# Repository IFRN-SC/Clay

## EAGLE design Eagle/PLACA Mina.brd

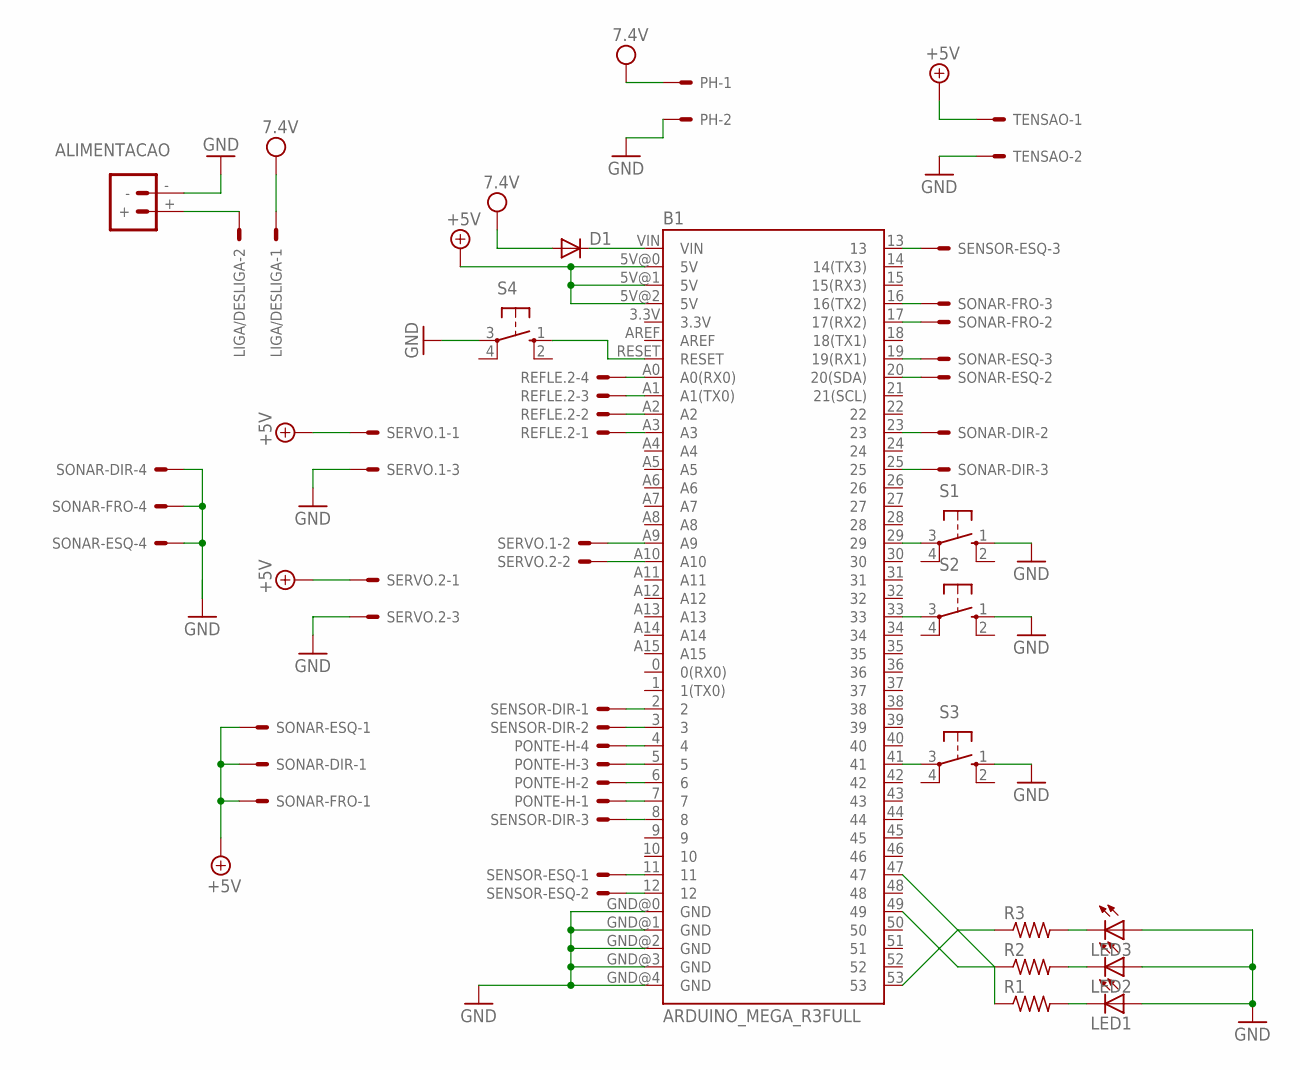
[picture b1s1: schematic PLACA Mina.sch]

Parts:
ALIMENTACAO: BATTERY_CONNXT60; XT60
B1: ARDUINO_MEGA_R3FULL; ARDUINO_MEGA
D1: 1N4004; DO41-10
LED1, LED2, LED3: LED5MM
LIGA/DESLIGA: CONN_0227-2021; 6410-02
PH: CONN_0227-2021; 6410-02
PONTE-H: CONN_0427-2041; 6410-04
R1, R2, R3: R-US_0204/7; 0204/7
REFLE.2: CONN_0427-2041; 6410-04
S1, S2, S3, S4: 10-XX; B3F-10XX
SENSOR-DIR: CONN_0327-2031; 6410-03
SENSOR-ESQ: CONN_0327-2031; 6410-03
SERVO.1, SERVO.2: CONN_0327-2031; 6410-03
SONAR-DIR: CONN_0427-2041; 6410-04
SONAR-ESQ: CONN_0427-2041; 6410-04
SONAR-FRO: CONN_0427-2041; 6410-04
TENSAO: CONN_0227-2021; 6410-02

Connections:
+5V: B1.5V@0 (5V), B1.5V@1 (5V), B1.5V@2 (5V), SERVO.1.1, SERVO.2.1, SONAR-DIR.1, SONAR-ESQ.1, SONAR-FRO.1, TENSAO.1
GND: ALIMENTACAO.-, B1.GND@0 (GND), B1.GND@1 (GND), B1.GND@2 (GND), B1.GND@3 (GND), B1.GND@4 (GND), LED1.A, LED2.A, LED3.A, PH.2, S1.1 (S), S2.1 (S), S3.1 (S), S4.3, SERVO.1.3, SERVO.2.3, SONAR-DIR.4, SONAR-ESQ.4, SONAR-FRO.4, TENSAO.2
unnamed: B1.A3, REFLE.2.1
unnamed: B1.A2, REFLE.2.2
unnamed: B1.A1 (A1(TX0)), REFLE.2.3
unnamed: B1.A0 (A0(RX0)), REFLE.2.4
unnamed: B1.16 (16(TX2)), SONAR-FRO.3
unnamed: B1.17 (17(RX2)), SONAR-FRO.2
unnamed: B1.7, PONTE-H.1
unnamed: B1.6, PONTE-H.2
unnamed: B1.5, PONTE-H.3
unnamed: B1.4, PONTE-H.4
unnamed: B1.20 (20(SDA)), SONAR-ESQ.2
unnamed: B1.19 (19(RX1)), SONAR-ESQ.3
unnamed: B1.23, SONAR-DIR.2
unnamed: B1.25, SONAR-DIR.3
unnamed: B1.11, SENSOR-ESQ.1
unnamed: B1.12, SENSOR-ESQ.2
unnamed: B1.13, SENSOR-ESQ.3
unnamed: B1.2, SENSOR-DIR.1
unnamed: B1.3, SENSOR-DIR.2
unnamed: B1.8, SENSOR-DIR.3
unnamed: B1.A10, SERVO.2.2
unnamed: B1.A9, SERVO.1.2
unnamed: B1.29, S1.3
unnamed: B1.33, S2.3
unnamed: B1.41, S3.3
unnamed: B1.53, R3.1
unnamed: B1.49, R2.1
unnamed: B1.47, R1.1
unnamed: LED1.K (C), R1.2
unnamed: LED2.K (C), R2.2
unnamed: LED3.K (C), R3.2
unnamed: B1.VIN, D1.C
unnamed: ALIMENTACAO.+, LIGA/DESLIGA.2
unnamed: B1.RESET, S4.1 (S)
VDD: D1.A, LIGA/DESLIGA.1, PH.1

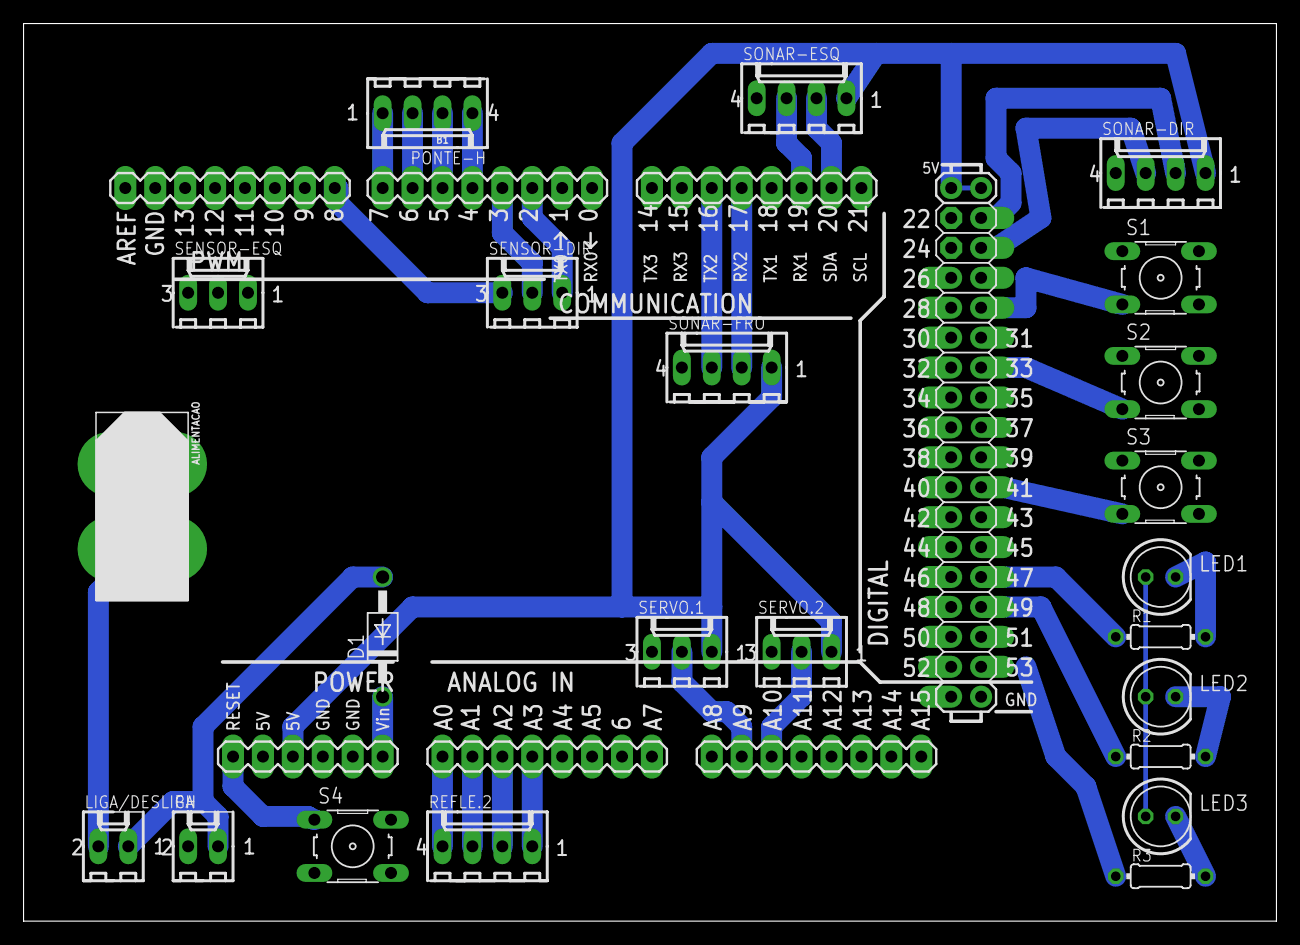
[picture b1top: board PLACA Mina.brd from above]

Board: 2 copper layers, 106.3 x 76.2 mm, 24 parts (0 on the bottom side), 37 nets.

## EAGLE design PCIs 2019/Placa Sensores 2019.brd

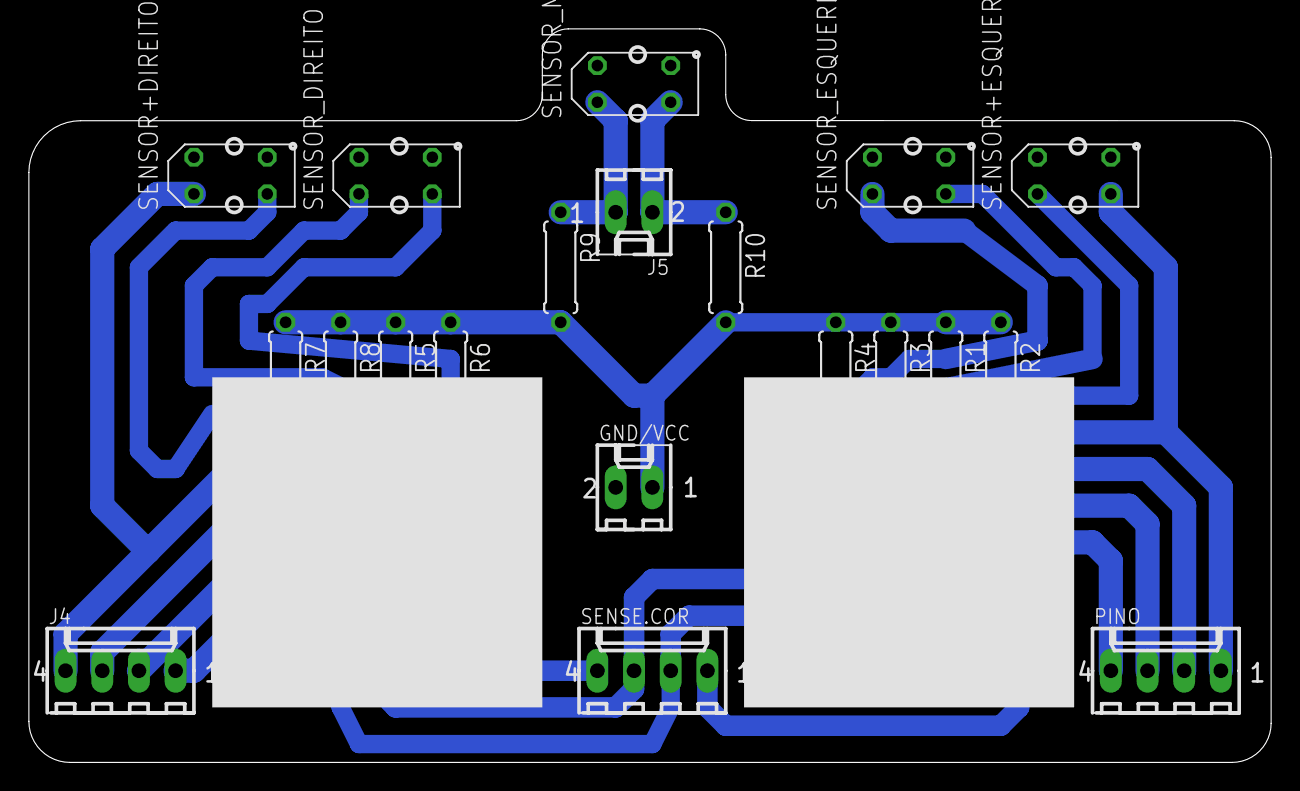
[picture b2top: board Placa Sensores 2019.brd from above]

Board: 2 copper layers, 86.0 x 50.8 mm, 22 parts (0 on the bottom side), 16 nets.

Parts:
GND/VCC: TENSÃO; 6410-02
J4: 6410-04
J5: 6410-02
PINO: 6410-04
R1, R2, R3, R4, R5, R6, R7, R8, R9, R10: 0207/7
SENSE.COR: 6410-04
SENSOR+DIREITO: TCRT5000
SENSOR+ESQUERDO: TCRT5000
SENSOR_DIREITO: TCRT5000
SENSOR_ESQUERDO: TCRT5000
SENSOR_MEIO: TCRT5000
TCS1, TCS2: TCS34725

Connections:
+5V: GND/VCC.1, R1.1, R2.1, R3.1, R4.1, R5.1, R6.1, R7.1, R8.1, R9.2, R10.2
GND: GND/VCC.2, SENSOR+DIREITO.E, SENSOR+DIREITO.K, SENSOR+ESQUERDO.E, SENSOR+ESQUERDO.K, SENSOR_DIREITO.E, SENSOR_DIREITO.K, SENSOR_ESQUERDO.E, SENSOR_ESQUERDO.K, SENSOR_MEIO.E, SENSOR_MEIO.K, TCS1.GND, TCS2.GND
unnamed: SENSE.COR.1, TCS1.VIN
unnamed: SENSE.COR.2, TCS1.SDA, TCS2.SDA
unnamed: SENSE.COR.3, TCS1.SCL, TCS2.SCL
unnamed: SENSE.COR.4, TCS2.VIN
unnamed: PINO.1, R2.2, SENSOR+ESQUERDO.C
unnamed: PINO.4, R4.2, SENSOR_ESQUERDO.A
unnamed: J4.2, R5.2, SENSOR_DIREITO.A
unnamed: PINO.2, R1.2, SENSOR+ESQUERDO.A
unnamed: PINO.3, R3.2, SENSOR_ESQUERDO.C
unnamed: J5.2, R10.1, SENSOR_MEIO.C
unnamed: J5.1, R9.1, SENSOR_MEIO.A
unnamed: J4.1, R6.2, SENSOR_DIREITO.C
unnamed: J4.4, R7.2, SENSOR+DIREITO.A
unnamed: J4.3, R8.2, SENSOR+DIREITO.C

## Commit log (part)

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2017-09-14 codigo arduino
2017-09-28 foi Criado um codigo para acionar um motor atraves da leitura de um sensor de refletancia
2018-04-11 Arquivo base do arduíno
2018-04-12 Inicio do código de estratégia, criado e iniciado os métodos seguir linha, verde, sala3, desviarObstaculo. Adionado linha reta
2018-04-12 Acrescentado uma estrutura condicional no método seguir linha
2018-04-12 Adicionada mais estruturas condicionais para seguir linha
2018-04-12 Nome alterado e esse arquivo foi excluído
2018-04-12 Alteração em algumas linhas e acrescimo do include
2018-04-23 Adicionando o objeto robo para pegar os metodos
2018-05-03 Apagados
2018-05-03 Alterado o robo hardware, criado e implementado funções na classe sensores.
2018-05-03 criado e implementado funções
2018-05-07 Retirado as classes
2018-05-07 Adicionada classes no cpp e h
2018-05-10 Adicionada as condições nas funções
2018-05-10 Modificada uma função
2018-05-10 Classe apagada
2018-05-10 Mudança nas funções
    Simplificou as funções, retirada as estruturas condicionais.
2018-05-10 Não compila
    Adicionado o objeto robô
2018-05-10 Não compila
    Criação de quatro variáveis do seguir linha
2018-05-14 Alterações as estruturais condicionais da classe Estrategia
2018-05-14 Criação da função atualizar e chamada dele nas funções seguintes
2018-05-14 Criação da função atualizar
2018-05-14 Identação do código
2018-05-14 Importação da classe sensores e criação do objeto sensores
2018-05-14 Atualização da Estrategia
    Chamado da função seguirLinha na função executa.
    Acréscimo do objeto nas estruturas condicionais.
2018-05-14 Atualização da classe estrategia.ino
    Importação da classe robo_hardware2.h e servo.h.
    Acréscimo do objeto estrategia e robo.configurar.
    Chamado da função executa.
2018-05-24 Modificado para dois sensores
2018-05-29 Classes novas
2018-05-29 Novas classes
2018-05-29 Desenho do chassi
2018-06-11 Modificação nas estruturais condicionais. Acréscimo de outras estruturas condicionais.
2018-06-11 Modificação na variável e na classe
2018-06-11 Exclusão da função senao
2018-06-11 Inicialização apagada
2018-06-11 remoção de linhas
2018-06-11 Criação da função que retorna verdadeiro quando os 4 sensores veem preto
2018-06-15 Criação das classes .h e . cpp de movimento
2018-06-15 Criação das classes .h e . cpp de Calibracao
2018-06-15 Simplicação da movimentação do robo
2018-06-15 Importação da classe movimento Criação do objeto Da classe movimento
2018-06-15 Comentário em várias linhas. Acréscimo do return com o POO
2018-06-15 Importação da classe calibracao. Criacao do objeto de calibracao
2018-07-27 Sincronia com o codigo do github Codigo de calibracao retirado da classe sensores
2018-07-31 Adicionado calibração
2018-07-31 adição e utilização classe movimento
    ass patolinio
2018-07-31 Utilização da calibração e adição de uma nova função
2018-07-31 eu fix e ta certo!
2018-07-31 calibralção variada: CINMESQ de 56 para 62 CINESQ 59 apra 72 CINDIR 59 para 68 CIMDIR 56 para 60
2018-08-01 estrategia verde
2018-08-13 Alterações de Minnael
    Minnael realizou alterações as quais ele não sabe o que fez ou não lembra.
2018-08-13 Adição de calibração
    Foi realizada modificações nas funções para utilizar o objeto calibração.
2018-08-13 Criação da classe movimento
    Criação de nova classe para utilizar funções pequenas e auto explicativas sobre a movimentação do robô
2018-08-13 Adição de novas classes/includes
    Includes nos arquivos de sensores.h, movimento.h e calibracao.h
2018-08-13 Alteração de girando: Tava -40 e Foi para -50.
2018-08-13 Girando: de -50 para -40
2018-08-13 MENU
    Função menu criada.
2018-08-14 adição de classes.
2018-08-14 adição do calibração semi-automatica.
2018-08-15 adição e edição de delays basicos.
2018-08-15 Alteração de calibração
2018-08-15 alteração de desviar de obstaculo que variou de <10 para <=10. ou seja mudou porra nenhuma
2018-08-15 adição de arquivos de PCI de cor
2018-08-15 adição
2018-08-17 CALIBRADOR
    Foi aadicionado a pasta "estrategia" do robô uma função de calibração.
2018-08-17 adi;'ao
2018-08-17 adi;'oes
2018-08-17 Commit dos arquivos em um novo branch
2018-08-24 adição de de nova função de movimento
2018-08-24 variação da função frente.
2018-08-24 irrelevante
2018-08-24 adição de novos delays && mudança de logica da função de obstaculo.
2018-08-24 mudança de pinagem
2018-08-24 todos explicados no branch pen_drive_minnael
2018-08-28 Arquivo excluído
2018-08-28 Criacao do .cpp do CalibradorGT
2018-08-28 Alterando a funcao calibrar. Criando funcoes do valor medio de cada sensor. Implementando na classe sensores a calibracao.
2018-08-29 adição de duas novas funções da classe movimento.
2018-08-29 troca de velocidade das funções da classe movimento.
2018-08-29 edição da função sala 3 && adição de configuração de sensor lateral.
2018-08-29 variação de calibração.
2018-09-06 LONDON 1.O
    -O codigo foi alterado, e automatizado, adicionando "menu" e "calibrador".
    -Correcao de bug na leitura do "sensor mais direito" na classe "calibracao".
2018-09-06 LONDON 1.1
    -Inclusao das novas classes.
2018-09-10 Correção de bugs
    Correção de bugs nos valores recebidos de "Calibracao". Robo não indetificava linha, todos os sensores eram atribuidos com zero, como foram criados dois objetos distintos.
2018-09-12 EEPROM
    Foi adicionado o EEPROM E "Desviar".
2018-09-13 CODIGO OBSTACULO E CALIBRACAO
    Alterado os delay do obstaculo e emplementado o "CalibradorGT" que pega valores de branco e preto de varias areas da arena.
2018-09-14 SALA TRÊS E DESVIAR
    Foi implementado o codigo que fará o robô subir a rampa, adicionado o comando que fará desviar de obstaculo e alinhar-se.
2018-09-17 ORGANIZACAO DA ESTRATEGIA
    Devido a confusao entre os nomes das classes "Calibrador" e a antiga "Calibracao" que faziam coisas totalmente diferentes o nome de "Calibracao" virou "Logica". foi feito uma identacao e organizacao 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
2018-09-18 METODOS MOVIMENTO PARA OBSTACULO
    Devido ao problema em editar os metodos de movimento padrao, que estes tambem fariam mudancas consideraveis no "desviar osbtaculo", foi criado metodos de movimentos apenas para o obstaculo.
2018-09-20 Inclusao da versao mais atual do material gt
2018-09-20 Exclusao da segunda vercao da classe sensores
2018-09-20 Criacao da sala3.h e .cpp Modificacao das classes sensores, movimento e estrategia exclusao do CalibradorGT
2018-09-21 adição do sensores_h
2018-09-21 mudança de movimento basicos
2018-09-21 mudança de movimento basicos. - inverter com o segundo commit atras
2018-09-21 sem mudanças.;..
2018-09-21 sem mudanças
2018-09-21 ultima parte mudanças basicas na classe estrategia e model0 de sala 3 antigo
2018-09-21 Correcao do return logica
2018-09-21 Alteracao teste da sala3
2018-09-21 Mudanca dos valores do movimento
2018-09-21 Alteracao,(errada), do menu
2018-09-21 Alteracao dos movimentos na classe estrategia
2018-09-25 Exclusao pela obsolescencia do codigo
2018-09-25 Modificacao da logica da classe sensores
2018-09-25 Modificacao dos movimentos
2018-09-25 Modificacao dos espacos
2018-09-28 Alteracao em algumas partes da funcao rampa
2018-09-28 identacao e comentarios no codigo.
2018-10-19 alteração basica de movimentos
2018-10-19 Alteração na classse estrategia
2018-10-19 alteração basica na classe movimento
2018-10-19 estrategia do verde incrivel
2018-10-25 adição do verde e alterações de comandos de movimento.
2018-10-26 adição de novos movimentos retilineos e proprios para o obstaculo. Obstaculo adicionado e funcionando medianamente.
2018-11-13 alterações no verde
2018-11-13 alterações basicas
2018-11-13 sala 3 alterações basicas
2019-02-12 Adicao do cod atual do repositorio principal
2019-02-12 Termino 1.0
2019-02-15 Codigo do GT master oficial
2019-02-22 Adição de novas variaveis de branco/preto
2019-02-22 Acdição de novas variaveis branco/preto
2019-02-22 Adição/refroma de controle
2019-02-22 adição de variavel (v) de controle
2019-02-22 adição da função/class (sala3)
2019-02-22 Commit PC
2019-02-22 Adição da primeira placa de sensores de 2019
2019-02-23 Priemeira PCI de 2019 terminada (5 sensores reflexivos, 2 sensores de cor + pinos para coletar os 3 valores precisos.
2019-02-23 Pdf + names + configs básicas
2019-02-23 reboot
2019-02-25 alteração no if do sensorBAixo
2019-02-25 Pequena alteraçãol de movimento frenlen
2019-03-07 Troca de estilo do desvio de obstaculo
2019-03-07 adição de novas variaveis dos sensores
2019-03-08 adição de novos comando para o desviar de obstaculo.
2019-03-08 alteração de movimento básica.
2019-03-11 Alterações de Minnael
2019-03-12 adição de novas congigs a função obstaculo
2019-03-12 alteração de movimento fren
2019-03-12 + uma atualização da função obstaculo.
2019-03-12 pequena alteração de movimento.
2019-03-13 obs alterações basics
2019-03-13 Alteração do obs
2019-03-13 alteração movimento frenbasic
2019-03-14 Variação da função redutor
2019-03-14 adição de novo metodo na classe sensores
2019-03-14 mudanças no obs/rampa
2019-03-15 obs ++
2019-03-15 obss tools
2019-03-19 adição de mais uma variante no private + início da sala3
2019-03-22 ++ PRE CALIBRACAO REDUTOR
2019-03-23 Troca de funções "Com ruido" para "Sem Ruido"
2019-03-27 Retirada da class sala3, mudança do metodo sala3 direto na class estrategia.
2019-03-31 PCI C.L.A.Y
2019-04-03 Adição/troca de class e logicas
2019-04-03 Varias mudanças em classes basicas + grandes mudanças no seguir linha (de if para while) + placa nova.
2019-04-04 Alteração de movimento para a melhora do desempenho da rampa.
2019-04-04 ++ANTERIOR
2019-04-05 Alteração no metodo obstaculo + alterações basicas nos delay da sala3(resgate.1).
2019-04-05 Obs++ (obs2.)
2019-04-05 ++OBS (obs.3)
2019-04-06 Ajuste de delays + obss++ (obs.4)
2019-04-09 Atualizações de delays sala3 + pequenas mudanças no metódo OBS.
2019-04-10 All ++
2019-04-10 +++ ALL
2019-04-11 Mudanças para a adequação do 5° sensor.
2019-04-13 Atualização no metodo seguir linha e na class sensores
2019-04-16 +++AAA seguir pré finalizado
2019-04-22 ++all
2019-04-23 ++OBS
2019-04-25 Commit final do dia. Da sequencia ++ALL. Mudanças em vários metódos como o mOBS, mSeguirLinha, mRedutor. (robo seguindo linha perfeitamente + OBS secundário)
2019-05-04 +++OOOBS
2019-05-07 Obs semi final++
2019-05-13 "R.I.P" Obstaculo fechado! Código faltanto apenas sala3/verde!
2019-05-15 R.I.P 15/05/2019 demorou a morer
2019-05-17 Ultimas avaliações nos metodos obstaculo e seguirlinha.
2019-05-23 Sem time
2019-05-24 Adição de fim de curso
2019-05-27 pequenas mudanças no metódo redutor.
2019-05-27 alteração classe movimento.
2019-05-29 Pequenos ajustes
2019-06-27 Adição de novas variaveis para o seguirlinha.
2019-08-01 Atualização de estrategia da sala3
2019-08-01 Atualização da estrategia da Sala3 + pequenas alterações básicas no metodo seguir linha.
2019-08-01 Organização de pastas
2019-08-01 Organização de pastas 2.0
2019-08-01 Adição do projeto fizz + pequeno código de seguir linha (para ele)
2019-08-14 Otimização da sala3
2019-08-14 Mudança de porta do fim do curso (no estrategia.h) e alterações de alto nivel na class sala3
2019-08-15 Rework sala3
2019-08-29 sala3 ++
2019-09-09 Sala3 Adaptada para fizz o robô de esteira
2019-09-10 2/6 Sala3 concluidoS! Pequena atualização na class estrategia (seguirLinha)
2019-09-12 ++Sala3 ++Estrategia
2019-09-13 adição de metodos de angu na class movimento, e implementação desses mesmos na Sala3
2019-09-18 alterações nos delays sala3
2019-09-20 configurações da garra
2019-09-25 ++ sala3
2019-09-26 ++sala3 //IHU IHU
2019-09-26 Configuração na class estrategia e ajustes na class Sala3.
2019-09-27 Sala 3++
2019-09-27 Sala3++
2019-09-30 Pequeno ajuste no seguir linha e ++sala3
2019-09-30 Sala3 +++
2019-10-08 class Estrategia otimizada, alterações nos metodos primarios de movimento, grandes alterações na class Sala3
2019-10-08 Sala3 otimizada, class movimento otimizada e calibrada e pequenas alterações na class strategy
2019-10-08 Adicionado configuraçãod e servo para a rampa, sala3++
2019-10-08 Sala3 ++ Estrategy ++
2019-10-10 sala3 ++ movimento ++
2019-10-11 ++ all
2019-10-14 dealays do seguir linhar excluidos, fluidez e precisão no seguirLinha. Porem altos riscos de perca de linha.
